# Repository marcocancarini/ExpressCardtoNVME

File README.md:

# ExpressCard → M.2 NVMe for the ThinkPad X230

An adapter that lets you use an **M.2 NVMe 2230 or 2242** SSD (M-key or B+M-key) in the **ExpressCard/54** slot
of a ThinkPad X230 (and in general in any ExpressCard slot with PCIe). It is a bare board, with no shell, that slides
straight into the slot. It is 70 mm long, like "short" ExpressCards: it sits flush with the slot instead of sticking out.

> **Status:** design complete and DRC-clean, **not yet manufactured or tested on hardware**.
> Before ordering, follow the *Checks before ordering* section of the [guide](GUIDE.md).

## Variants

| Variant | Form factor | USB | Notes |
|---|---|---|---|
| `EC2M2_34` | ExpressCard/34 (34 × 70 mm) | no | fits /34 and /54 slots |
| `EC2M2_34_USB5V` | ExpressCard/34 | yes, 5 V | USB pads on the left side, next to the M.2 |
| `EC2M2_54` | ExpressCard/54 (L-shaped, 54 × 70 mm) | no | more stable in a /54 slot |
| `EC2M2_54_USB5V` | ExpressCard/54 | yes, 5 V | USB pads + cut-out to house a small USB receiver |

| 34 mm | 34 mm + USB | 54 mm | 54 mm + USB |
|---|---|---|---|
|  |  |  |  |

The ExpressCard and M.2 connectors have no 3D model in the library: only their pads show up in the renders.

## Features

- **PCIe x1** from the ExpressCard slot to the M.2 connector (M-key, 3.2 mm height); differential pairs at **~87 Ω**
  (computed with an included 2D field solver, `gen/impedance.py`).
- **Screw mounting** for the SSD: two M2 SMT nuts (H 1.0 mm) at the 2230 and 2242 positions.
- SSD **activity LED** and an optional **CLKREQ#→GND jumper** for SSDs that are not detected.
- **USB versions:** the slot's USB 2.0 port is brought out to pads, with a **3.3 → 5 V boost** (TPS61240, 200 mA guaranteed)
  because the ExpressCard slot does not provide 5 V. The power block sits in the free strip to the left of the SSD. A **separate 3.3 V pad** (3V3) is for 3.3 V devices
  or measurements; it is placed away from the 5V pad so the two cannot be confused.
- 2 layers, 1.0 mm thick, JLCPCB-compatible rules; BOM with LCSC part numbers and assembly-ready files.
- On the back: a small **QR code** linking to this repository.
- **3D-printable case** for transport and storage (see below).

## Printable case

In the slot the board must be used **bare**: the ExpressCard slot is 5.0 mm tall and board + SSD already reach about 4.85 mm,
so there is no room for a shell. The case is for carrying and storing it with the SSD installed: the board slides in
from the open side, two small bumps hold it in place and the notches let you grab it.

- Ready-made STLs: `out/enclosure/EC2M2_34_case.stl` (38 × 72 × 8.4 mm) and `EC2M2_54_case.stl` (58 × 72 × 8.4 mm).
- Editable source: `out/enclosure/enclosure.scad` (OpenSCAD), or the parameters in `gen/enclosure.py`.
- Print it **standing on its open side**: no supports or long bridges. PLA or PETG, 0.2 mm layers, 3 perimeters.

## Repository contents

```
gen/                 generator and tools
  gen_board.py       builds the PCB of one variant (KiCad 10 Python API)
  build.sh           generates the 4 variants + DRC
  fab.sh             Gerbers, drill, CPL, renders, 1:1 PDF, JLCPCB files
  render.sh          3D renders into docs/img
  check_nets.py      checks the netlist against the expected mapping
  impedance.py       differential pair impedance calculation (requires scipy)
  jlc_search.py      LCSC/JLC part number search
  jlc_files.py       JLC-format BOM/CPL + component cost estimate
  enclosure.py       3D-printable case (STL + OpenSCAD)
out/<variant>/       KiCad project (.kicad_pcb/.kicad_pro/.kicad_dru), BOM, footprint library
  fab/               Gerbers, drill, CPL, 1:1 PDF, quick renders
  jlcpcb/            Gerber zip, BOM and CPL for JLCPCB, cost estimate
out/enclosure/       case STLs and OpenSCAD source
docs/img/            renders
GUIDE.md             checks, ordering, assembly, first boot
HANDOFF.md           design notes: pinout, choices, calculations
```

## Regenerating the files

You need KiCad 10 with the footprint libraries (`kicad-library`) and Python 3.

```sh
gen/build.sh        # generates the 4 variants and runs the DRC
gen/fab.sh          # production and JLCPCB files
gen/render.sh       # renders (also needs kicad-library-3d)
```

For impedance and the case: `python3 -m venv gen/.venv && gen/.venv/bin/pip install scipy manifold3d trimesh matplotlib`.
Case: `gen/.venv/bin/python gen/enclosure.py`. Impedance:
`gen/.venv/bin/python gen/impedance.py 0.4,0.15,0.25` (width, spacing between traces, distance to GND, in mm).

## Indicative cost

Only the components assembled by JLCPCB (API prices, October 2026): about **$10** for 5 boards without USB, **$17** with USB,
plus the PCB, assembly setup and shipping. Details in `out/<variant>/jlcpcb/<variant>_estimate.md`.
The ExpressCard connector is not available from LCSC: it must be bought separately and soldered by hand.

## Known issues and sourcing notes

- **J1 (ExpressCard connector) sourcing.** Not on LCSC. The correct part family is the FCI/Amphenol
  **10030570-21xxLF** "CONN EXPRESSCARD MOD CARD 26POS" (e.g. **10030570-2112LF**: RS 615-9467, Digi-Key 1001395;
  26 pos, 1 row, 1.0 mm pitch, right-angle SMT, housing 34 × 5 × 11 mm), or the TE Connectivity ExpressCard
  module connector. A cheap practical source is a **donor ExpressCard** (e.g. USB 3.0 ExpressCard/34 cards on
  AliExpress, ~$9): desolder the 26-pin connector with hot air. Note: the BOM comment in `gen/gen_board.py`
  mentions "JAE PX10" — that is a 1.0 mm board-to-board series, **not** an ExpressCard connector; disregard it.
  Always check the real connector against `fab/<variant>_print_1to1.pdf` printed at 100 % (pads, pin 1, stop).
- **Netclass diff-pair defaults** in the generated `.kicad_pro` (width 0.3 / gap 0.2) do not match the actual
  pair geometry (width 0.4 / gap 0.15); the tracks have explicit widths, so this is cosmetic only.
- **Known design limits** (details in HANDOFF.md): REFCLK runs on B.Cu over the GND plane (impedance not
  controlled there), M.2 pins 51 and 67 left NC, no series AC capacitors on the PCIe pairs (they are on the
  host and the SSD).
- **Verification status:** DRC clean and `check_nets.py` OK on all 4 variants; regenerating with
  `gen/build.sh` reproduces the committed files (modulo UUIDs/timestamps). Still **not manufactured or tested
  on hardware** — follow the checks in GUIDE.md before ordering.

## License

This project (hardware design, documentation and scripts) is released under the
[Creative Commons Attribution-NonCommercial-ShareAlike 4.0 International](https://creativecommons.org/licenses/by-nc-sa/4.0/)
license (CC BY-NC-SA 4.0). You may build, modify and share it for **non-commercial** purposes, crediting the author and
releasing derivative works under the same license. Selling boards or derivatives requires permission from the author.
See [LICENSE](LICENSE).

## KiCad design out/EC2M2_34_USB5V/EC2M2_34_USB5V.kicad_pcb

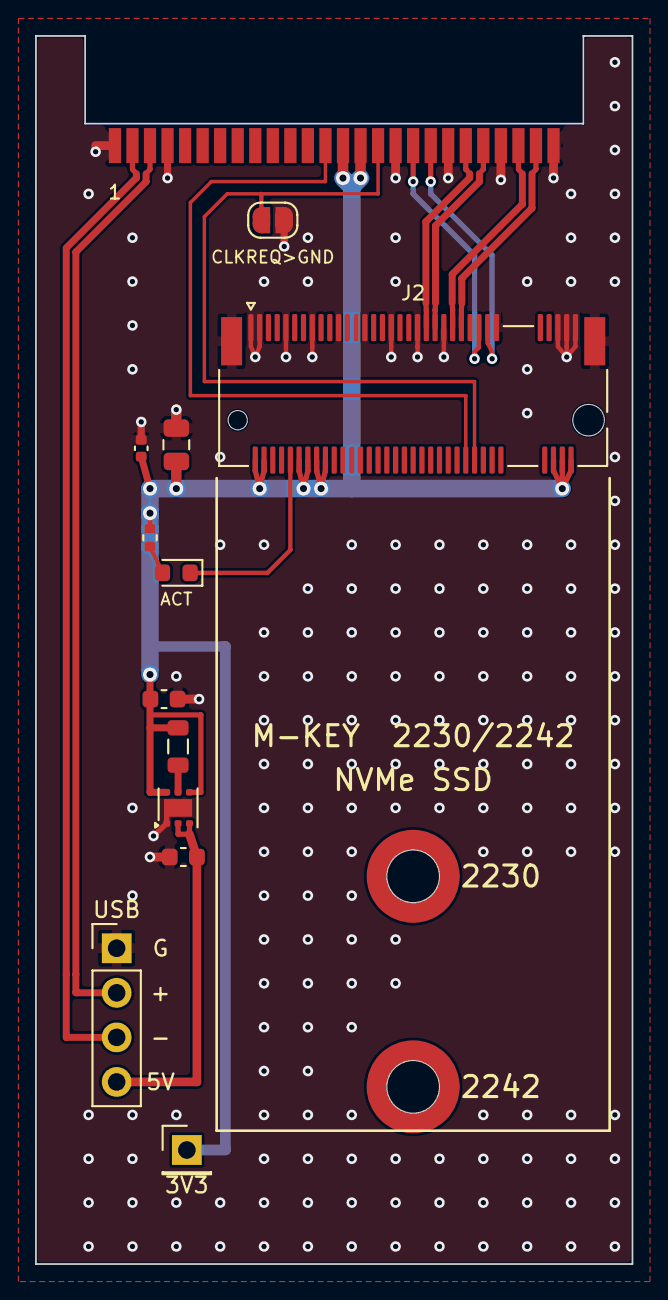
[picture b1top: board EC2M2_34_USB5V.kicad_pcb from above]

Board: 2 copper layers, 34.0 x 70.0 mm, 15 parts (0 on the bottom side), 16 nets.

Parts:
C1: 22uF; C_0805_2012Metric
C2: 100nF; C_0402_1005Metric
C3, C4: 10uF; C_0603_1608Metric
D1: LED red; LED_0603_1608Metric
H1, H2: M2 SMT nut H1.0; Mounting_Wuerth_WA-SMSI-M2_H1mm_9774010243
J1: ExpressCard 26P; ExpressCard_Module_1x26_P1.0mm
J2: M.2 M-key H3.2; TE_M.2_M_2x38-1MP_P0.5mm
J3: USB pads; PinHeader_1x04_P2.54mm_Vertical
J4: 3V3 pad; PinHeader_1x01_P2.54mm_Vertical
JP1: CLKREQ-GND; SolderJumper-2_P1.3mm_Open_RoundedPad1.0x1.5mm
L1: 1uH; L_0805_2012Metric
R1: 470; R_0402_1005Metric
U1: TPS61240DRV; WSON-6-1EP_2x2mm_P0.65mm_EP1x1.6mm

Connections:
+3V3: C1.1, C2.1, C3.1, J1.14, J1.15, J2.2, J2.4, J2.12, J2.14, J2.16, J2.18, J2.70, J2.72, J2.74, J4.1, L1.2, R1.2, U1.4, U1.6
+5V: C4.1, J3.4, U1.2, U1.3
CLKREQ#: J1.16, J2.52, JP1.1
GND: C1.2, C2.2, C3.2, C4.2, J1.1, J1.4, J1.17, J1.20, J1.23, J1.26, J2.1, J2.3, J2.9, J2.15, J2.21, J2.27, J2.33, J2.39, J2.45, J2.57, J2.71, J2.73, J2.75, J2.MP, J3.1, JP1.2, U1.1, U1.7
LED#: D1.1, J2.10
LED_A: D1.2, R1.1
PERST#: J1.13, J2.50
PERn0: J1.21, J2.41
PERp0: J1.22, J2.43
PETn0: J1.24, J2.47
PETp0: J1.25, J2.49
REFCLK+: J1.19, J2.55
REFCLK-: J1.18, J2.53
SW: L1.1, U1.5
USB_D+: J1.3, J3.2
USB_D-: J1.2, J3.3

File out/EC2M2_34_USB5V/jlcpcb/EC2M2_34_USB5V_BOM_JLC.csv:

Comment,Designator,Footprint,LCSC Part #
22uF,C1,C_0805_2012Metric,C45783
100nF,C2,C_0402_1005Metric,C1525
10uF,"C3,C4",C_0603_1608Metric,C19702
LED red,D1,LED_0603_1608Metric,C2286
M2 SMT nut H1.0,"H1,H2",Mounting_Wuerth_WA-SMSI-M2_H1mm_9774010243,C5360192
M.2 M-key H3.2,J2,TE_M.2_M_2x38-1MP_P0.5mm,C52766481
1uH,L1,L_0805_2012Metric,C76793
470,R1,R_0402_1005Metric,C25117
TPS61240DRV,U1,WSON-6-1EP_2x2mm_P0.65mm_EP1x1.6mm,C59567
